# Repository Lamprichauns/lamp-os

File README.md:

# LampOS

A platform for retrofitting traditional desk lamps with programmable LED controllers to build unique lighted art structures. Using standardized and user friendly hardware based on the ubiquitous ESP32, Neopixels and common sensors, this project seeks to simplify the job of building curious and surreal LED projects for the community to enjoy.

## Lamp Personality & Behaviours

The vision for the lamps is that they remain mostly still and static, as a contrast to the plethora of sound reactive and blinky light art out there. The brightness of the lamps and the colorful glowing base draws attention to the juxtaposition of an ordinary household object in extraordinary places.

Within this vision there is room for the lamps to have personality, shown through subtle behaviour based on things like time, randomness, sensor data, presence/absence of other lamps, etc.

With these sorts of subtle changes, people may begin to realize things are not as static as they seem, creating a somewhat complex puzzle for people to solve and talk about.

## Selecting a lamp to convert

## Lamp Hardware Requirements

This software is intended for the ESP32 platform. Our preferred dev board is an ESP32-WROOM32 30 Pin board variant measuring no wider than 28mm with a chip antenna. Unsoldered/unwelded pins are preferred if possible. This space requirement is so the board can fit comfortably into a standard lamp socket. The boards can be had easily from Amazon and AliExpress for $5-10. The model we use has this pinout <https://lastminuteengineers.com/esp32-pinout-reference/>

The USB connector is a USB type A metal shell crimp on connector. These tend to be the most robust.

By default, a lamp will use about 80 LEDs. The limiting factor at the moment is current draw. generally over 100 LEDs you may have stability issues with a conventional USB source. We recommend purchasing LEDs strips with the following specs:

- Around 2m in length
- SK6812 chipset
- IP67 waterproof
- 5VDC
- RGBWW (warm white) LED Strips
- Spacing of 60 LEDs/m

A 10000mAh battery pack with USB will run this device portably for around 7 hours

You'll also need some basic workshop tools, heat shrink, wire connectors, a soldering iron and a way to print the plastic bulb

There's a handy [build guide with images here](hardware/build/README.md)

## Lamp OS

More details about Lamp OS and other supporting tools can be found in the [software](software/) folder

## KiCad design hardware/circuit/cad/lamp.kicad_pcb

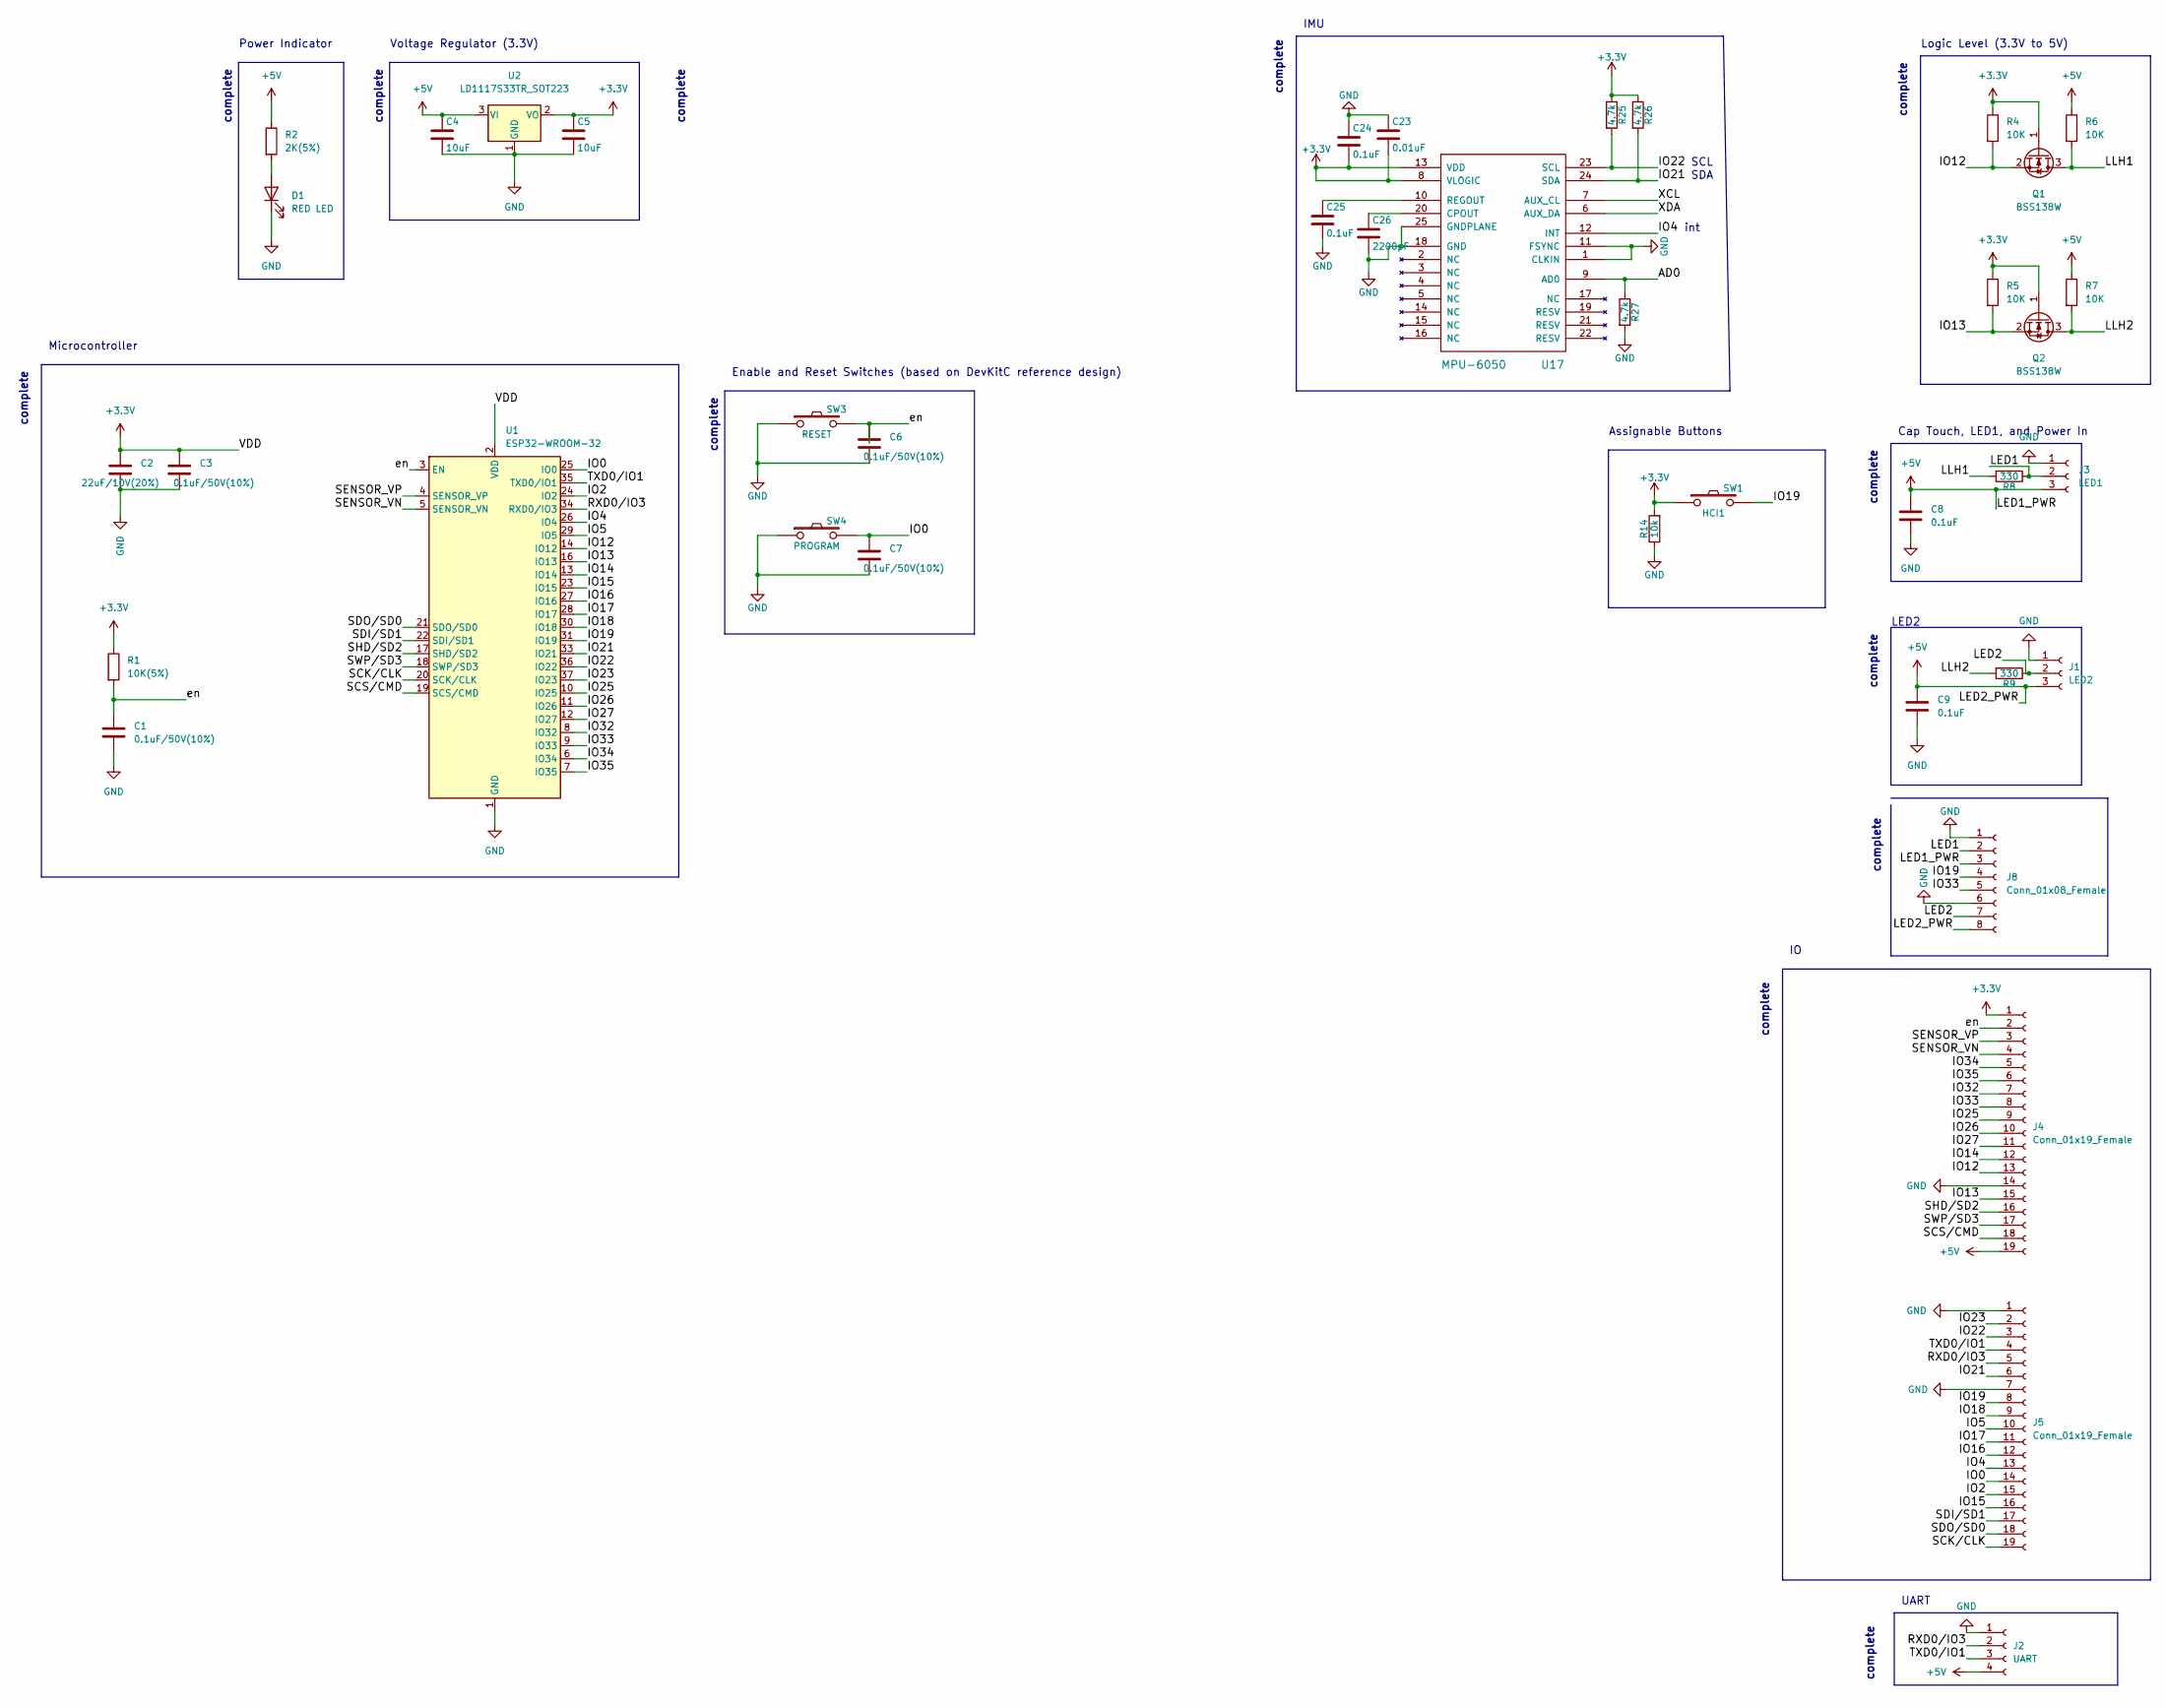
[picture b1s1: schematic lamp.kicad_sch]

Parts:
C1, C3, C6, C7: 0.1uF/50V(10%); C_1206_3216Metric
C2: 22uF/10V(20%); C_1206_3216Metric
C4, C5: 10uF; C_1206_3216Metric
C8, C9, C24, C25: 0.1uF; C_1206_3216Metric
C23: 0.01uF; C_1206_3216Metric
C26: 2200pF; C_1206_3216Metric
D1: RED LED; LED_1206_3216Metric
J1: LED2; PinHeader_1x03_P2.54mm_Vertical
J2: UART; PinHeader_1x04_P2.54mm_Vertical
J3: LED1; PinHeader_1x03_P2.54mm_Vertical
J4, J5: Conn_01x19_Female; PinHeader_1x19_P2.54mm_Vertical
J8: Conn_01x08_Female; TerminalBlock_Phoenix_PT-1,5-8-3.5-H_1x08_P3.50mm_Horizontal
Q1, Q2: BSS138W; SOT-323_SC-70
R1: 10K(5%); R_1206_3216Metric
R2: 2K(5%); R_1206_3216Metric
R4, R5, R6, R7: 10K; R_1206_3216Metric
R8, R9: 330; R_1206_3216Metric
R14: 10k; R_1206_3216Metric
R25, R26, R27: 4.7k; R_1206_3216Metric
SW1: HCI1; SW_SPST_PTS645
SW3: RESET; SW_SPST_PTS645
SW4: PROGRAM; SW_SPST_PTS645
U1: ESP32-WROOM-32
U2: LD1117S33TR_SOT223; SOT-223-3_TabPin2
U17: MPU-6050; QFN-24-1EP_4x4mm_P0.5mm_EP2.7x2.7mm

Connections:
+3V3: C2.1, C3.1, C5.1, C23.2, C24.2, J4.1, Q1.1 (G), Q2.1 (G), R1.1, R4.1, R5.1, R14.2, R25.1, R26.1, SW1.1, U1.2 (VDD), U2.2 (VO), U17.8 (VLOGIC), U17.13 (VDD)
+5V: C4.1, C8.1, C9.1, J1.3, J2.4, J3.3, J4.19, J8.3, J8.8, R2.1, R6.1, R7.1, U2.3 (VI)
/AD0: R27.1, U17.9 (AD0)
/IO0: C7.1, J5.14, SW4.2, U1.25 (IO0)
/IO2: J5.15, U1.24 (IO2)
/IO4: J5.13, U1.26 (IO4), U17.12 (INT)
/IO5: J5.10, U1.29 (IO5)
/IO12: J4.13, Q1.2 (S), R4.2, U1.14 (IO12)
/IO13: J4.15, Q2.2 (S), R5.2, U1.16 (IO13)
/IO14: J4.12, U1.13 (IO14)
/IO15: J5.16, U1.23 (IO15)
/IO16: J5.12, U1.27 (IO16)
/IO17: J5.11, U1.28 (IO17)
/IO18: J5.9, U1.30 (IO18)
/IO19: J5.8, J8.4, SW1.2, U1.31 (IO19)
/IO21: J5.6, R26.2, U1.33 (IO21), U17.24 (SDA)
/IO22: J5.3, R25.2, U1.36 (IO22), U17.23 (SCL)
/IO23: J5.2, U1.37 (IO23)
/IO25: J4.9, U1.10 (IO25)
/IO26: J4.10, U1.11 (IO26)
/IO27: J4.11, U1.12 (IO27)
/IO32: J4.7, U1.8 (IO32)
/IO33: J4.8, J8.5, U1.9 (IO33)
/IO34: J4.5, U1.6 (IO34)
/IO35: J4.6, U1.7 (IO35)
/LED1: J3.2, J8.2, R8.1
/LED2: J1.2, J8.7, R9.1
/LLH1: Q1.3 (D), R6.2, R8.2
/LLH2: Q2.3 (D), R7.2, R9.2
/RXD0/IO3: J2.2, J5.5, U1.34 (RXD0/IO3)
/SCK/CLK: J5.19, U1.20 (SCK/CLK)
/SCS/CMD: J4.18, U1.19 (SCS/CMD)
/SDI/SD1: J5.17, U1.22 (SDI/SD1)
/SDO/SD0: J5.18, U1.21 (SDO/SD0)
/SENSOR_VN: J4.4, U1.5 (SENSOR_VN)
/SENSOR_VP: J4.3, U1.4 (SENSOR_VP)
/SHD/SD2: J4.16, U1.17 (SHD/SD2)
/SWP/SD3: J4.17, U1.18 (SWP/SD3)
/TXD0/IO1: J2.3, J5.4, U1.35 (TXD0/IO1)
/XCL: U17.7 (AUX_CL)
/XDA: U17.6 (AUX_DA)
/en: C1.1, C6.1, J4.2, R1.2, SW3.2, U1.3 (EN)
GND: C1.2, C2.2, C3.2, C4.2, C5.2, C6.2, C7.2, C8.2, C9.2, C23.1, C24.1, C25.2, C26.2, D1.1 (K), J1.1, J2.1, J3.1, J4.14, J5.1, J5.7, J8.1, J8.6, R14.1, R27.2, SW3.1, SW4.1, U1.1 (GND), U1.15 (GND), U1.38 (GND), U1.39 (GND), U2.1 (GND), U17.1 (CLKIN), U17.11 (FSYNC), U17.18 (GND), U17.25 (GNDPLANE)
unnamed: C25.1, U17.10 (REGOUT)
unnamed: C26.1, U17.20 (CPOUT)
unnamed: D1.2 (A), R2.2

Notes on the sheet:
Microcontroller
complete
UART
LED2
IMU
SCL
Logic Level (3.3V to 5V)
SDA
Enable and Reset Switches (based on DevKitC reference design)
Power Indicator
Cap Touch, LED1, and Power In
int
Voltage Regulator (3.3V)
Assignable Buttons

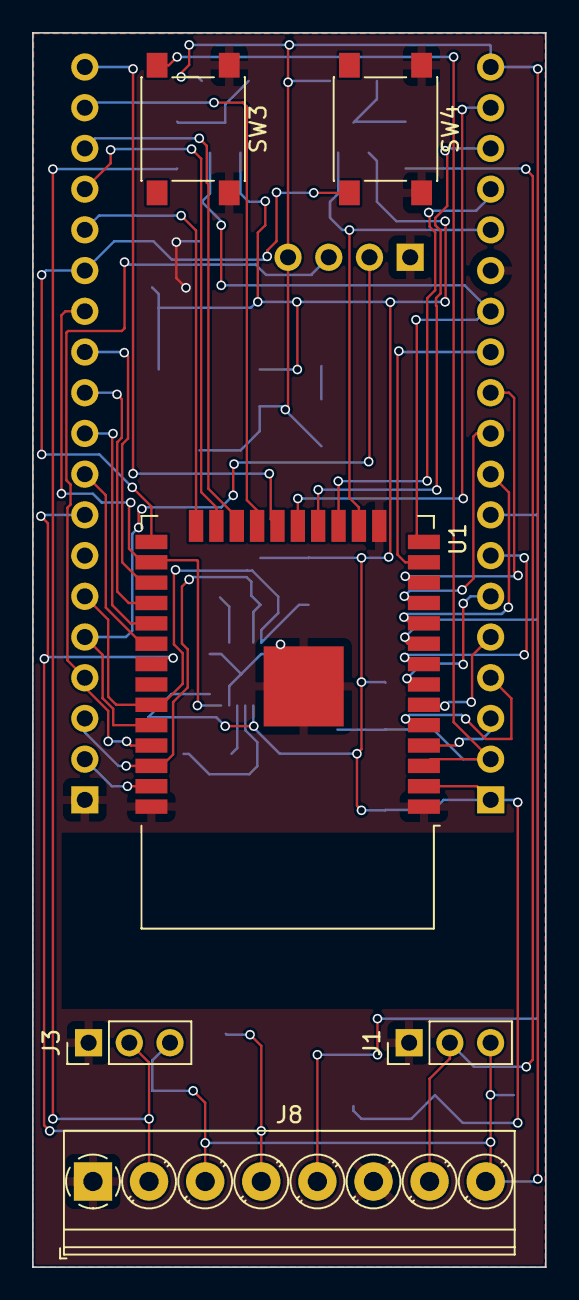
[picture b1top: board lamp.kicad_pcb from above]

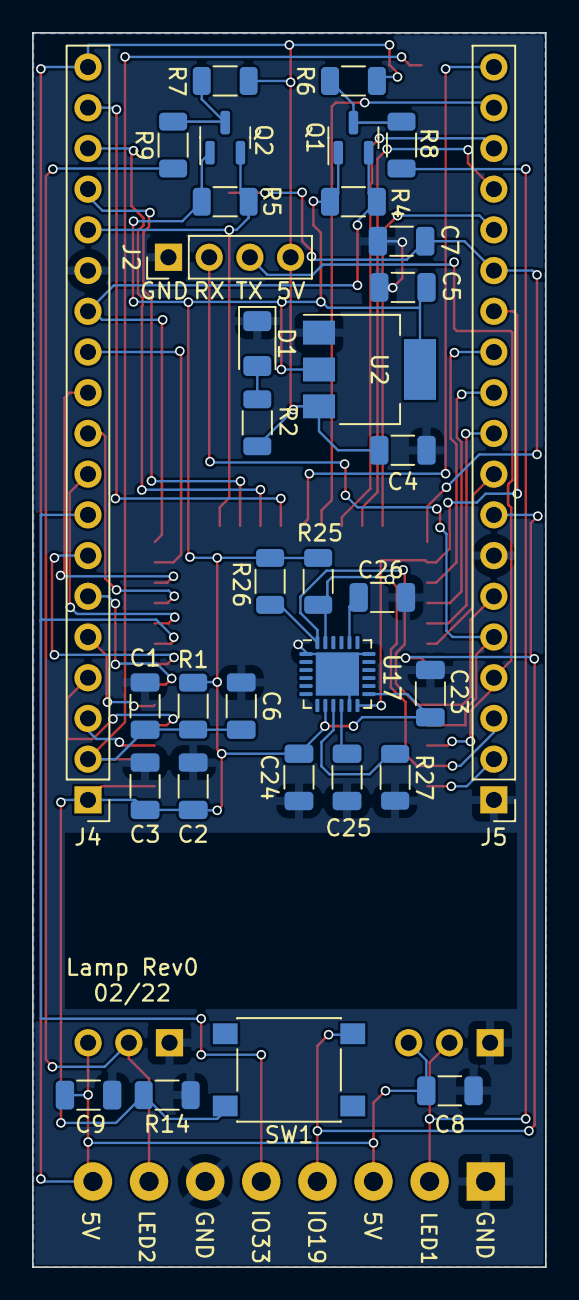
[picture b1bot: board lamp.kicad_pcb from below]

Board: 2 copper layers, 32.0 x 77.0 mm, 40 parts (34 on the bottom side), 44 nets.

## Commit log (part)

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2025-09-14 Adding UI to main lamp os project
2025-09-14 adding stage mode check
2025-09-14 adding an npm job for uploading to the board. removing comments from the build for more space savings. updating npm
2025-09-14 Adding more lifecycle events to artnet
2025-09-14 a few more wifi and bluetooth tweaks
2025-09-14 updating some configs on the artnet repeater. removing unneccessary flag for new artnet data
2025-09-14 updating use of config in init
2025-09-15 Adding lamp.local mdns entry. fixing cors
2025-09-15 Adding changes to enable OTA programming
2025-09-15 removing stage mode. upping shade pixels to 38 to support an older lamp
2025-09-15 reverting changes to stage mode in the UI. fixing logo embed in the c++ build
2025-09-16 splitting artifacts for easier use with esp32 web tools
2025-09-16 updating app to remove shade pixel config, since we'll all be using a similar bulb 3d model. updating defaults to match the c++ values
2025-09-16 uploading skeleton for web formatter tool
2025-09-16 touching up offsets and docs page
2025-09-16 updating dmx interpretation to be slow so lamps still appear quite still even while reacting to frenetic stage palettes
2025-09-17 slowing the animations down even more: now 4-12s
2025-09-17 Updating the lamp protocol to use 10 channels for each slot. Allowing the lamps to occupy 8 slots
2025-09-17 Add SSID-based home mode detection
    - Add homeModeSSID configuration parameter to lamp settings
    - Implement WiFi network scanning to detect configured home SSID
    - Home mode behaviors are now activated based on network presence rather than just configuration
    - Maintains backward compatibility: if no SSID is configured, home mode works as before
    - Clean architecture: home mode calculation happens outside compositor, keeps compositor simple
    - Periodic updates: home mode state is recalculated every 5 seconds when SSID-based mode is enabled
2025-09-17 reorganization to have colors seperate and introduce home mode ssid config
2025-09-18 home mode brightness
2025-09-18 condensing
2025-09-18 updating artnet functions to cache a little more. Adding a reconnect param and disabling sleep mode on the artnet repeater
2025-09-18 updating distribution on gh pages
2025-09-19 updating the web ui in preparation for wifi password updates
2025-09-20 Adding UI components and password management to SoftAP
2025-09-20 adding a higher resolution LUT for fades
2025-09-20 Updating some cppcheck recs and moving the lut to a resolution of 512 samples
2025-09-20 touching up linear ease math to match the quad function
2025-09-21 Updating distribution file
2025-09-22 further smoothing DMX transitions when the stage is being active
2025-09-22 fixing location of interlace job
2025-09-24 Removing interlacing as it was causing neopixel crashes. Adding a comparator to see if pixels actually need to be updated
2025-09-24 updating main distro
2025-09-24 configurable expressions - glitch, pulse, shifty
2025-09-24 Remove .vscode/settings.json from tracking
2025-09-24 expressions in full
2025-09-24 dup docs and fix
2025-09-24 tweaks to config
2025-09-24 remove debug code
2025-09-25 moving stuff around
